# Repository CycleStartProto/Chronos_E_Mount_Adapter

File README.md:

# Chronos E-Mount Lens Adapter

An active Sony E-mount lens adapter for the **Kron Technologies Chronos 1.4 and Chronos 2.1** high-speed cameras.

The adapter bolts to the front of the Chronos body and gives it a working female E-mount with full electronic control of the lens. A small RP2040 control board pretends to be a Sony camera body: it powers the lens, runs the E-mount serial protocol, and lets you drive **aperture and focus from buttons**, with live lens status shown on an OLED screen.

---

## Contents

- [Features](#features)
- [Photos](#photos)
- [What's needed to build](#whats-needed-to-build)
- [Manufacturing the PCBs](#manufacturing-the-pcbs)
- [Repository layout](#repository-layout)
- [Architecture](#architecture)
- [Firmware](#firmware)
- [Sourcing the mount: dismantling a Meike extension tube](#sourcing-the-mount-dismantling-a-meike-extension-tube)
- [Printing the parts](#printing-the-parts)
- [Lens contacts: the weakest part of the design](#lens-contacts-the-weakest-part-of-the-design)
- [Assembly overview](#assembly-overview)
- [Known issues and limitations](#known-issues-and-limitations)

---

## Features

- Female Sony E-mount on Chronos 1.4 / 2.1 bodies, with correct back focus
- Full electronic lens control. The board acts as the camera body on the E-mount bus.
- **Aperture** open/close in 1/3-stop steps
- **Focus**, either by the lens's own focus ring (focus-by-wire passthrough) or by buttons with a smooth speed ramp
- **Graceful eject**: the lens parks itself and powers down before you remove it
- **Hot-unplug safe**: removing the lens cuts power at once, from an interrupt
- 128×64 OLED status display showing lens name, focal length, f-number, focus position and distance
- Powered over USB-C from the camera's own USB port

## Photos

| | |
|---|---|
|  |  |
| Mount face with the lens off. The bayonet ring and lugs come from a Meike extension tube. | The row of lens contact springs sits just inside the bayonet. |
|  |  |
| Lens off, ready to mount. | Status display: lens, f-number, focus position, distance, OSS and focus mode. |
|  |  |
| The USB-C cable runs from the control board to the Chronos USB port. | Grip side. The adapter keeps a low profile under the lens. |

## What's needed to build

This is a personal project, and not intended to be a product. 

Everything needed to build one is in this repo apart from a few bought parts and tools.

The adapter consists **two 3D-printed parts and two PCBs**, plus parts harvested from a Meike E-mount extension tube set.

it is a fairly simple build, but does require a 3d printer, some high precision soldering, and handling of very tiny parts.

| Part | Type | Description |
|---|---|---|
| Adapter plate | 3D print | Bolts to the Chronos front, carries the E-mount bayonet and the contact flex, and sets the back focus |
| Cover | 3D print | Encloses the control board and holds the OLED window and buttons |
| E-mount interface (`EMountIface`) | Flat-flex PCB | Carries the lens contact springs and connects them to the control board |
| Control board | PCB | RP2040 lens controller, power switching, buttons, USB-C |
| [SSD1306 0.96" 128×64 I²C OLED module](https://a.co/d/0h7kQ9I0) | Bought part | Status display. It plugs into the control board's 4-pin header (address `0x3C`). |
| 1×10 pin header, 2.54 mm pitch | Bought part | Joins the flat flex to the control board (see below) |
| [Meike E-mount auto-focus extension tube set](https://a.co/d/0dT2TBgD) | Donor part | One tube provides the bayonet lugs, the tension springs and the electrical contact springs. The second tube is kept whole as a test fixture for setting the contacts. |
| USB-C cable | Bought part | Powers the control board from the Chronos USB port |

### Connecting the flat flex to the control board

The flat flex and the control board each have a matching row of ten 2.54 mm through-hole pads (Würth 61301011121 footprint). They are joined with a short piece of **1×10 straight pin header**:

1. Solder the pin header into the flat flex pcb.
2. Slide the flat-flex tail over the main control board so that pin 1 lines up on both boards.
3. Solder the the pins to the main control board, and trim off the excess pin length.

This makes a permanent, low-profile joint. To take the adapter apart later you'll need to desolder it, so finish the contact setup (see [Lens contacts](#lens-contacts-the-weakest-part-of-the-design)) before you solder it in for good.

### Control board hardware

- **RP2040** MCU with 16 MB W25Q128 QSPI flash and a 12 MHz crystal
- **USB-C** input (power and MicroPython REPL), with an NCP1117 3.3 V regulator
- Two P-MOSFET high-side switches: one for **lens logic power (3.3 V)** and one for **lens motor power (5 V)**
- 1812 PTC fuse on the input
- 10-pin header footprint (J2) for the E-mount flat flex
- 4-pin header for the **SSD1306 128×64 OLED** module (I²C)
- 6 side-actuated buttons: aperture open/close, focus down/up, OSS toggle, eject
- LIS3DH accelerometer (not used by the firmware; can be left off to allow JLCPCB's Economic assembly)

## Manufacturing the PCBs

Both boards were made by **[JLCPCB](https://jlcpcb.com)** from the design files in `hardware/pcbs/`. Almost everything is left at JLCPCB's default settings; the exceptions are listed below.

### Control board

Upload `hardware/pcbs/control_board_CAM_Output.zip` (the Gerbers and drill file exported from Fusion Electronics) to JLCPCB's PCB quote page.

- **PCB thickness: 1.0 mm.** This is the only setting to change. Everything else (2-layer FR-4, finish, colour and so on) can stay at JLCPCB's defaults, it would look better as black solder mask, but I wasn't going to wait the extra 2 days.
- **Assembly: turn on PCB Assembly** and export a BOM and pick-and-place (CPL) file from `control_board.sch` / `control board.brd` for it. The RP2040 (QFN-56) and the other fine-pitch parts are much easier to have assembled than to solder by hand.
- **Standard vs Economic assembly:** as designed, the board has to go through JLCPCB's **Standard** assembly service, because the LIS3DH accelerometer can't be placed on the Economic line. The firmware doesn't use the accelerometer, so if you mark it as **do not populate** (remove it from the BOM/CPL), you can choose the cheaper **Economic** service instead.
- Hand-solder the through-hole headers (flat flex and OLED) after the boards arrive.

### E-mount interface (flat flex)

- Order `EMountIface.brd` as a **flex PCB** from JLCPCB, exporting its Gerbers from Fusion Electronics in the same way as for the control board.
- **All default settings, no stiffener.**
- The flex has no components on it apart from the hand-soldered contact springs and the pin header joint, so it doesn't need assembly.

## Repository layout

```
firmware/
  main.py                  MicroPython lens driver (copy to the RP2040)
hardware/
  mechanical/              Fusion 360 (.f3d) and STEP models
    adapter plate.*          printed part
    cover.*                  printed part
    control board.*          PCB model, for fit checks
    EMountIface.*            flat-flex PCB model, for fit checks
  pcbs/                    Eagle / Fusion Electronics schematics and boards
    control_board.sch / control board.brd
    EMountIface.sch / EMountIface.brd
    control_board_CAM_Output.zip   Gerbers for the control board
pictures/                  Full-resolution build photos
```

## Architecture

```
 ┌──────────────┐  USB-C (5 V)  ┌────────────────────────────────────────┐
 │  Chronos     │──────────────▶│ Control board                          │
 │  USB port    │               │                                        │
 └──────────────┘               │  RP2040 ── I²C ── SSD1306 OLED         │
                                │    │  └── GPIO ── 6 buttons            │
                                │    │                                   │
                                │    ├─ GP6 ─▶ Q2 ─▶ LOGIC_VCC (3.3 V)   │
                                │    ├─ GP7 ─▶ Q3 ─▶ LENS_PWR  (5 V)     │
                                │    ├─ UART0 TX/RX ─┐                   │
                                │    ├─ B_CS / L_CS ─┤ E-mount bus       │
                                │    ├─ VD (60 Hz) ──┤                   │
                                │    └─ LENS_DET ◀───┘                   │
                                └──────────────────┬─────────────────────┘
                                                   │ 10-pin connector
                                        ┌──────────▼──────────┐
                                        │ EMountIface flat    │
                                        │ flex + contact      │
                                        │ springs             │
                                        └──────────┬──────────┘
                                                   │ ~2 mm air gap
                                        ┌──────────▼──────────┐
                                        │  Sony E-mount lens  │
                                        └─────────────────────┘
```

The control board stands in for a Sony body. The E-mount bus carries:

| Signal | Direction | Purpose |
|---|---|---|
| `B_TO_L_TXD` / `L_TO_B_RXD` | body ↔ lens | Half-duplex-style UART, 750 kbaud at start-up, then up to 1.5 Mbaud |
| `B_CS_L` / `L_CS_B` | body → lens / lens → body | Chip-select handshake lines that frame each exchange |
| `BODY_VD_LENS` | body → lens | 60 Hz vertical-sync pulse. The lens runs its control loop in step with it. |
| `LENS_DET` | lens → body | Pulled low when a lens is mounted |
| `LENS_PWR`, `LOGIC_VCC` | body → lens | Switched 5 V motor supply and 3.3 V logic supply |

### RP2040 pin map

| GPIO | Function |
|---|---|
| GP0 / GP1 | UART0 TX / RX to the lens |
| GP2 / GP3 | `L_CS_B` (in) / `B_CS_L` (out) |
| GP4 | `LENS_DET` (low = lens attached) |
| GP5 | `BODY_VD_LENS` 60 Hz sync (PWM) |
| GP6 | Lens logic power enable (low = on) |
| GP7 | Lens motor power enable (driven low = on, input = off; **never drive high**) |
| GP8 / GP9 | Aperture open / close buttons |
| GP10 / GP11 | OLED SDA / SCL (I2C1) |
| GP12 / GP13 | Focus down / up buttons |
| GP14 | OSS toggle button |
| GP15 | Eject button |
| GP16–21 | LIS3DH accelerometer (SPI, unused) |

## Firmware

The firmware is a single MicroPython file, [`firmware/main.py`](firmware/main.py). Flash MicroPython onto the RP2040, then copy `main.py` to the board, for example with Thonny or `mpremote cp firmware/main.py :main.py`. It runs at boot.

### State machine

```
  no lens ──(LENS_DET low, 150 ms debounce)──▶ power on
     ▲                                             │
     │                                     pin handshake
     │                                             │
     │                                             ▼
     │                                     init sequence ──(fail)──▶ error ─(1 s)─┐
     │                                             │                              │
     │                                             ▼                              │
     │                                  60 Hz run loop ◀───────────────────────────┘
     │                                             │
     ├──────────(lens pulled: hard IRQ cuts power)─┤
     │                                             │
     └──(lens removed)── ejected ◀──(EJECT button: graceful shutdown)
```

1. **Detect and power up.** When `LENS_DET` stays low for 150 ms, the board switches on the lens logic and motor supplies, starts the 60 Hz VD signal, and opens the UART at 750 kbaud.
2. **Pin handshake.** The lens signals it is ready by pulling RXD low and raising `L_CS`. The board answers by raising and then dropping `B_CS`. This sequence was measured on a real lens, and the firmware follows it.
3. **Init sequence.** The board sends the same set of messages a Sony A6000 sends: `0x01, 0x07, 0x0C, 0x0B, 0x08, 0x09, 0x0D, 0x10, 0x0A`. Along the way it reads the lens ID, focal-length range and aperture range, and it switches the bus to 1.5 Mbaud if the lens supports it (`0x0C`). It aborts on the same conditions a real body does.
4. **Run loop.** Each frame the lens sends status messages (`0x05`, `0x06`), and the board answers with control messages (`0x03`, `0x04`):
   - `0x03` carries the requested aperture, in 1/3-stop steps, and the data-row index the body wants back.
   - `0x04` carries the focus command. By default it sends **"focus follow"** (`0x81`), which hands focus to the lens's own focus ring. While a focus button is held, it switches to absolute move commands with a speed ramp (crawl to full speed over about 1 s), then stops and hands control back to the ring.
5. **Eject.** Pressing EJECT follows the power-off sequence of a Sony body: send `0x0A` with an all-zero payload, then `0x16`, and wait for the lens to park and acknowledge. The board then cuts motor power, drops `B_CS`, waits for RXD to fall, and cuts logic power. The lens stays off until it is removed or EJECT is pressed again.
6. **Hot unplug.** A hard interrupt on `LENS_DET` going high switches off both supplies and tri-states the bus lines straight away, using register writes only, so an unpowered lens is never back-fed.

### Design notes

- **Non-blocking display.** The OLED is updated one 128-byte page at a time between lens frames, so drawing the screen never makes the lens loop miss a frame.
- **Allocation-free hot paths.** RX and TX use preallocated buffers and `memoryview`s to keep the garbage collector out of the 60 Hz loop.
- **Tunables** at the top of `main.py` cover baud rate limits, timeouts, focus speed and ramp, aperture button repeat rate, I²C speed and debug logging.
- **Diagnostics.** Setting `PIN_HS_TRACE = True` logs every handshake line change with microsecond timestamps. This is useful for checking a new lens.

### Protocol sources

The protocol work builds on community reverse-engineering of the Sony E-mount bus, including the *E-mount protocol RE* notes, the LexOptical E-Mount firmware and traffic captures, and our own captures and measurements on a Sony SELP1650.

### Tested lenses

| Lens | Status |
|---|---|
| Sony E PZ 16-50mm f/3.5-5.6 OSS (SELP1650) | Working |
| Sony E 55-210mm f/4.5-6.3 OSS (SEL55210) | Working |
| Sigma 16mm F1.4 DC DN, model 402965 (shown in the photos) | Working |
| Sigma 30mm F1.4 DC DN, model 302965 | Working |

If you try another lens, please open an issue with the result. A `PIN_HS_TRACE` log helps if it fails.

## Sourcing the mount: dismantling a Meike extension tube

Rather than machining a bayonet, this design takes the precision metal parts from an inexpensive **[Meike E-mount auto-focus extension tube](https://a.co/d/0dT2TBgD)**. The tube's lens-side (female) end already contains everything a body-side E-mount needs:

- the **bayonet ring with its lugs**, which carries the lens's weight and clocking
- the **tension (leaf) springs** on the back of the ring, which pull the lens flange tight against the mount face
- the **electrical contact springs**, which touch the lens's gold pads

The tube also has a lock pin and release lever, but this build doesn't use them (see [Why there is no lock pin](#why-there-is-no-lock-pin)).

### Teardown

1. **Pick one tube to dismantle.** The Meike set comes with two tubes. Take one apart for parts and **keep the other one whole**: it is used as a stand-in lens when you set the contacts.
2. **Remove the front-face screws.** The female mount face is held by four M2 countersunk screws on a 52 mm bolt circle. Use a good-fitting JIS/Phillips #0 driver. The screws are small and strip easily.
3. **Lift off the bayonet ring.** Take care to keep the **leaf tension springs** on its back face. These are what keep the lens seated with no play, so don't bend them.
4. **Remove the contact block** and free the **contact springs** from it. These are the parts that touch the lens pads, and they get soldered onto the flat-flex PCB later.
5. Keep all the screws. The bayonet ring goes back together on the printed adapter plate using the same screws and hole pattern. The lock pin and release lever can be set aside.

The adapter plate copies the hole pattern and clocking of the Meike mount face, so the harvested ring and screws drop straight in.

### Why there is no lock pin

On a normal E-mount body (and in the extension tube), a spring-loaded pin pops up into a notch in the lens flange once the lens is rotated home. That stops the lens from turning back out until you press the release button. The pin needs a few millimetres of depth behind the mount face for its own travel and its spring.

Here there is only about 2 mm between the mount ring and the Chronos body (see [Lens contacts](#lens-contacts-the-weakest-part-of-the-design)), and the contact flex already takes up most of it. There isn't enough throw for the pin to retract fully when the lens is turning and then spring out far enough to catch, so I couldn't get it to work reliably and left it out.

Without the pin, the lens is held by the bayonet lugs and the leaf-spring tension. In practice this is plenty: focusing and normal handling don't move the lens. Just rotate the lens fully home when mounting, and don't carry the camera by the lens.

## Printing the parts

There are two printed parts: the **adapter plate** and the **cover**. STEP files are in `hardware/mechanical/`.

**Recommended material: carbon-fiber-reinforced polycarbonate (PC-CF).**

- The adapter plate holds the full weight of the lens and sets the back focus. It has to stay stiff and keep its size, and PC-CF creeps far less than PLA or PETG under constant load.
- The Chronos body gets warm in use, and polycarbonate's high heat-deflection temperature keeps the mount from softening or warping.
- The carbon fill gives a matte, non-reflective finish, which helps keep stray light down around the sensor opening.

**Alternative: carbon-fiber-reinforced PETG (PETG-CF)** may also be a good candidate. It's easier to print than PC-CF (lower temperatures, less warping, and no enclosure needed), and the carbon fill still adds a lot of stiffness. Its heat resistance and creep resistance are lower than PC-CF's, so it is a reasonable choice if you can't print polycarbonate well, but PC-CF is still preferred for the adapter plate.

Print the adapter plate with the mount face flat on the bed for the best flatness. Use a hardened nozzle for CF filaments. Check the back focus after printing; small changes in the plate's thickness show up directly as focus error at infinity.

## Lens contacts:

**The electrical contacts to the lens are the most fragile part of this build.**

The E-mount has a short 18 mm flange distance, and the Chronos sensor sits deep enough that, to get the back focus right, **there is only about a few mm of space between the lens and the Chronos body.** That few mm has to hold the adapter plate's mount face, the flat-flex PCB, and the contact springs. There is no room for an off-the-shelf pogo-pin block or for the extension tube's original contact housing.

The solution was a thin **flat-flex PCB** (`EMountIface`) with the harvested Meike contact springs soldered straight onto it. This is a hand-fitting job:

1. **Solder the springs** onto the pads of the flat-flex PCB, one per E-mount contact.
2. **UV-cure glue** the flex and springs into the slot in the adapter plate so that the springs stand in the correct positions behind the contact window.
3. **Cut the springs short** so they reach just past the mount face. They should touch the lens pads without stopping the lens from rotating into the bayonet.
4. **Bend** each spring so it will press on the center of its pad once a lens is locked in.
5. **Mount the spare Meike tube as if it were a lens.** Its rear (male) end has the same gold contact pads in the same positions as a real lens, and those pads are wired straight through to the contact springs on its front (female) end.
6. **Check each contact with a continuity tester**, from the spring on the front of the spare tube to the matching pin on the 10-pin header. Because the tube's pads sit exactly where a lens's would, a good reading proves that each spring is touching the *right* pad with real pressure, not just touching something. Also check that no pin is shorted to its neighbours.
7. Remove the tube, re-bend any spring that failed, and repeat until every contact passes.

Using the spare tube instead of a real lens means you're not probing, or scratching, the contacts of an expensive lens, and the probe points on the tube's front face are easy to reach. Expect to iterate on steps 3–7 several times. If the lens fails to initialise, or drops out intermittently, check these contacts first. A spring that is slightly too short gives intermittent connection, and one that is too long can snag the lens pads when mounting.

## Assembly overview

1. Print the adapter plate and cover in PC-CF (or PETG-CF).
2. Order the control board and the `EMountIface` flat flex from JLCPCB (see [Manufacturing the PCBs](#manufacturing-the-pcbs)).
3. Dismantle one Meike extension tube as described above, and keep the second one whole.
4. Install the bayonet ring and leaf springs on the adapter plate with the original M2 screws. The lock pin is not used.
5. Fit the contact springs to the flat flex, glue it into the adapter plate, and set the springs using the spare tube (see [Lens contacts](#lens-contacts-the-weakest-part-of-the-design)).
6. Join the flat flex to the control board with the 1×10 pin header, then mount the board and the SSD1306 OLED in the cover.
7. Flash MicroPython and `firmware/main.py`.
8. Mount the adapter on the Chronos and connect the control board to the camera's USB port with a USB-C cable.
9. Mount a lens. The OLED should show the lens name and f-number within a second or two.

## Known issues and limitations

- **Lens contacts** are hand-fitted and are the most likely point of failure (see above).
- **No lens lock pin.** The lens is held by the bayonet and leaf springs only (see [Why there is no lock pin](#why-there-is-no-lock-pin)).
- **OSS (image stabilisation) and power-zoom** are not controllable. No OSS on/off or zoom command has been found in any public protocol source. The OSS button toggles a placeholder (`OSS_FIELD = None`) until the field is found.
- **Lens power switch rework.** On the current control board, R11 must be removed so that Q3 (lens motor power) can actually turn off. GP7 then connects straight to a gate that R10 pulls up to 5 V, which is outside the RP2040's rating. A planned fix replaces R16 with a BAT54 Schottky diode (cathode to GP7). The firmware never drives GP7 high, and must not.
- **No external pull-up on `L_TO_B_RXD`.** The firmware uses the RP2040's internal pull-up. A 10–47 kΩ external pull-up is recommended on the next board revision.
- Four lenses have been tested so far (see [Tested lenses](#tested-lenses)). Others should work but are unconfirmed.

---

*Not affiliated with Sony, Kron Technologies or Meike. E-mount is a trademark of Sony Corporation.*

*Huge Thanks To LexOptical, without the e mount traffic samples and reverse engineering repos, this would not have been possible*

*mechanical and electrical design beyond the e mount itself is my own, Firmware and docs were made with heavy assistance from Claude*

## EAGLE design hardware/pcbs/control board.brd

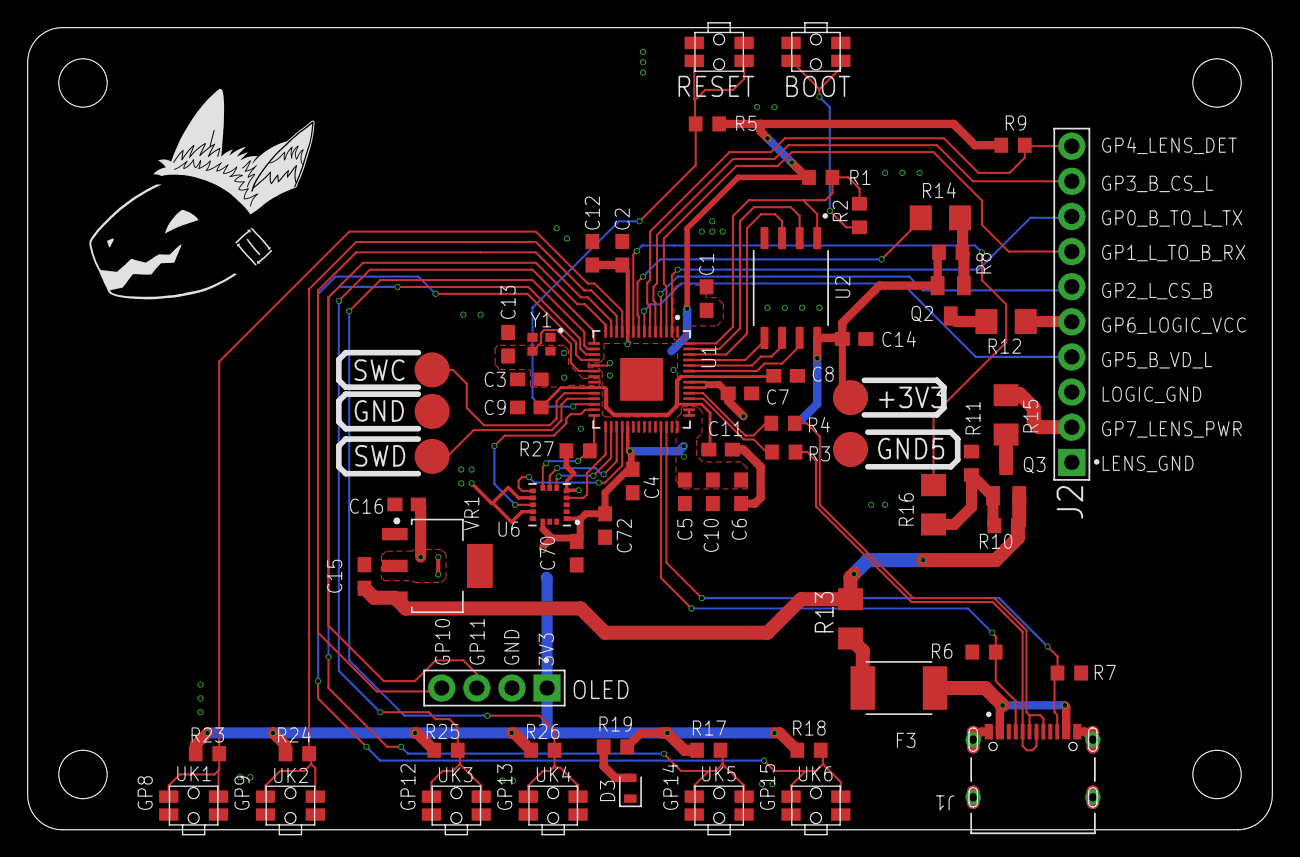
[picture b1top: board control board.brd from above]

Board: 2 copper layers, 90.0 x 58.0 mm, 68 parts (0 on the bottom side), 52 nets.

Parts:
+3V3: TPB2,54; B2,54
BOOT: SKSCLDE010
C1, C2, C3, C4, C5, C6, C7, C8, C9, C13, C14, C70: 100n; C0603
C10, C11: 1u; C0603
C12, C15, C16, C72: 10u; C0603
D3: LED_WHITE; LEDC1608X35N_FLAT-B
F3: 1812L010; FUSC4532X125
GND, GND5: TPB2,54; B2,54
J1: TYPE-C-31-M-12; HRO_TYPE-C-31-M-12
J2: 61301011121
OLED: 61300411121
Q2, Q3: SI2301CDS-T1-GE3; SOT23
R1, R5, R8, R9, R11, R17, R18, R23, R24, R25, R26, R27: 10k; R0603
R2: 1K; R0603
R3, R4: 27R; R0603
R6, R7, R10, R19: 5.1k; R0603
R12, R13, R14, R15, R16: 0; R1206
RESET: SKSCLDE010
SWC: TPB2,54; B2,54
SWD: TPB2,54; B2,54
U1: RP2040; QFN40P700X700X90-57N
U2: W25Q128JVSIQ; SOIC127P790X216-8N
U6: LIS3DHTR; XDCR_LIS3DHTR
U$2: CYCLESTARTV2MEDIUM
UK1, UK2, UK3, UK4, UK5, UK6: SKSCLDE010
VR1: NCP1117ST33T3G; SOT230P700X170-4
Y1: 12MHz; WE-SPXO_IQXO-540

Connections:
+1V1: C8.1, C9.1, C11.1, U1.23, U1.45, U1.50
+3.3V: +3V3.TP, C1.1, C2.1, C3.1, C4.1, C5.1, C6.1, C7.1, C10.1, C12.1, C13.1, C14.1, C16.1, C70.1, C72.1, OLED.1, Q2.2, R1.2, R5.2, R8.2, R9.2, R17.2, R18.2, R19.2, R23.2, R24.2, R25.2, R26.2, U1.1, U1.10, U1.22, U1.33, U1.42, U1.43, U1.44, U1.48, U1.49, U2.8, U6.1, U6.14, VR1.2, Y1.4
+5V: C15.1, Q3.2, R10.1, R13.2, VR1.3
AC_CK: U1.29, U6.4
AC_CS: R27.2, U1.28, U6.8
AC_INT0: U1.27, U6.11
AC_INT1: U1.32, U6.9
AC_SDI: U1.30, U6.6
AC_SDO: U1.31, U6.7
BODY_VD_LENS: J2.4, U1.7
B_CS_L: J2.9, U1.5
B_TO_L_TXD: J2.8, U1.2
GND: BOOT.1, BOOT.2, C1.2, C2.2, C3.2, C4.2, C5.2, C6.2, C7.2, C8.2, C9.2, C10.2, C11.2, C12.2, C13.2, C14.2, C15.2, C16.2, C70.2, C72.2, D3.C, GND.TP, GND5.TP, J1.A1_B12, J1.B1_A12, J1.S1, J1.S2, J1.S3, J1.S4, J2.1, J2.3, OLED.2, R6.1, R7.1, R11.1, R27.1, RESET.1, RESET.2, U1.19, U1.57, U2.4, U6.5, U6.10, U6.12, UK1.1, UK1.2, UK2.1, UK2.2, UK3.1, UK3.2, UK4.1, UK4.2, UK5.1, UK5.2, UK6.1, UK6.2, VR1.1, Y1.2
LENS_DET: J2.10, R9.1, U1.6
LENS_PWR: J2.2, R15.1
LOGIC_VCC: J2.5, R12.1
L_CS_B: J2.6, U1.4
L_TO_B_RXD: J2.7, U1.3
unnamed: D3.A, R19.1
unnamed: R14.2, U1.8
unnamed: BOOT.3, BOOT.4, R2.1
unnamed: R16.1, U1.9
unnamed: R5.1, RESET.3, RESET.4, U1.26
unnamed: Q2.3, R12.2
unnamed: Q2.1, R8.1, R14.1
unnamed: Q3.3, R15.2
unnamed: Q3.1, R10.2, R11.2, R16.2
unnamed: R17.1, U1.17, UK5.3, UK5.4
unnamed: R18.1, U1.18, UK6.3, UK6.4
unnamed: F3.1, J1.A4_B9, J1.B4_A9
unnamed: R23.1, U1.11, UK1.3, UK1.4
unnamed: R24.1, U1.12, UK2.3, UK2.4
unnamed: R25.1, U1.15, UK3.3, UK3.4
unnamed: R26.1, U1.16, UK4.3, UK4.4
OLSCL: OLED.3, U1.14
OLSDA: OLED.4, U1.13
QSPI_SCLK: U1.52, U2.6
QSPI_SD0: U1.53, U2.5
QSPI_SD1: U1.55, U2.2
QSPI_SD2: U1.54, U2.3
QSPI_SD3: U1.51, U2.7
QSPI_SS: R1.1, R2.2, U1.56, U2.1
SWCLK: SWC.TP, U1.24
SWD: SWD.TP, U1.25
USB1_N: R3.1, U1.46
USB1_P: R4.1, U1.47
USB2_N: J1.A7, J1.B7, R3.2
USB2_P: J1.A6, J1.B6, R4.2
USBCC1: J1.A5, R6.2, U1.39
USBCC2: J1.B5, R7.2, U1.40
VUSB: F3.2, R13.1
XIN: U1.20, Y1.3

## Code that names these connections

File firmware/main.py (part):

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# --------------------------------------------------------------------------
# Pin map (control_board.sch)
# --------------------------------------------------------------------------
PIN_TXD = const(0)      # B_TO_L_TXD   J2-8   UART0 TX
PIN_RXD = const(1)      # L_TO_B_RXD   J2-7   UART0 RX
PIN_LCS = const(2)      # L_CS_B       J2-6   lens->body CS (input, unused)
PIN_BCS = const(3)      # B_CS_L       J2-9   body->lens CS (output)
PIN_DET = const(4)      # LENS_DET     J2-10  10k pull-up (R9); low = lens on
PIN_VD = const(5)       # BODY_VD_LENS J2-4   60 Hz frame sync
PIN_LOGIC = const(6)    # Q2 gate, 10k pull-up: low = LOGIC_VCC on
PIN_PWR = const(7)      # Q3 gate: output low = LENS_PWR on, input = off
PIN_SDA = const(10)     # OLED (I2C1)
PIN_SCL = const(11)

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def _det_irq(pin):
    # Hard IRQ: register writes only, no heap allocation.
    global _removed
    mem32[_GPIO_OE_CLR] = _BIT_PWR      # GP7 -> input: LENS_PWR off
    mem32[_GPIO_OUT_SET] = _BIT_LOGIC   # GP6 high: LOGIC_VCC off
    mem32[_GPIO_OE_SET] = _BIT_LOGIC
    # Tri-state TXD, B_CS_L and VD so an unpowered lens is not back-fed.
    mem32[_GPIO_OE_CLR] = _BITS_SIG
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def lens_power_on():
    global _removed
    _removed = False
    pwr.init(Pin.OUT, value=0)      # drive low -> Q3 on -> LENS_PWR
    logic.init(Pin.OUT, value=0)    # drive low -> Q2 on -> LOGIC_VCC


def lens_power_off():
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            self.trace.append((time.ticks_diff(time.ticks_us(), self.t_t0), text))

    def _tpoll(self):
        st = mem32[_GPIO_IN] & 0x06            # bit 1 RXD, bit 2 L_CS_B
        if st != self.t_last:
            self.t_last = st
            self.trace.append((time.ticks_diff(time.ticks_us(), self.t_t0),
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          2. 0x16 (payload 01), wait for any 0x16 reply; the lens parks
             (power-zoom retract, focus) *before* it replies
          3. cut the motor supply (LENS_PWR)
          4. drop B_CS_L, UART off, TXD/RXD back to plain GPIO
          5. wait for the lens to pull RXD low (body: 5 ms polls, ~30 s max)
          6. drive TXD low; then the caller cuts LOGIC_VCC"""
        self.ui.eject_req = False
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

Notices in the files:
parts and their libraries:
Wurth_Quartz Crystals: Copyright: Würth Elektronik
